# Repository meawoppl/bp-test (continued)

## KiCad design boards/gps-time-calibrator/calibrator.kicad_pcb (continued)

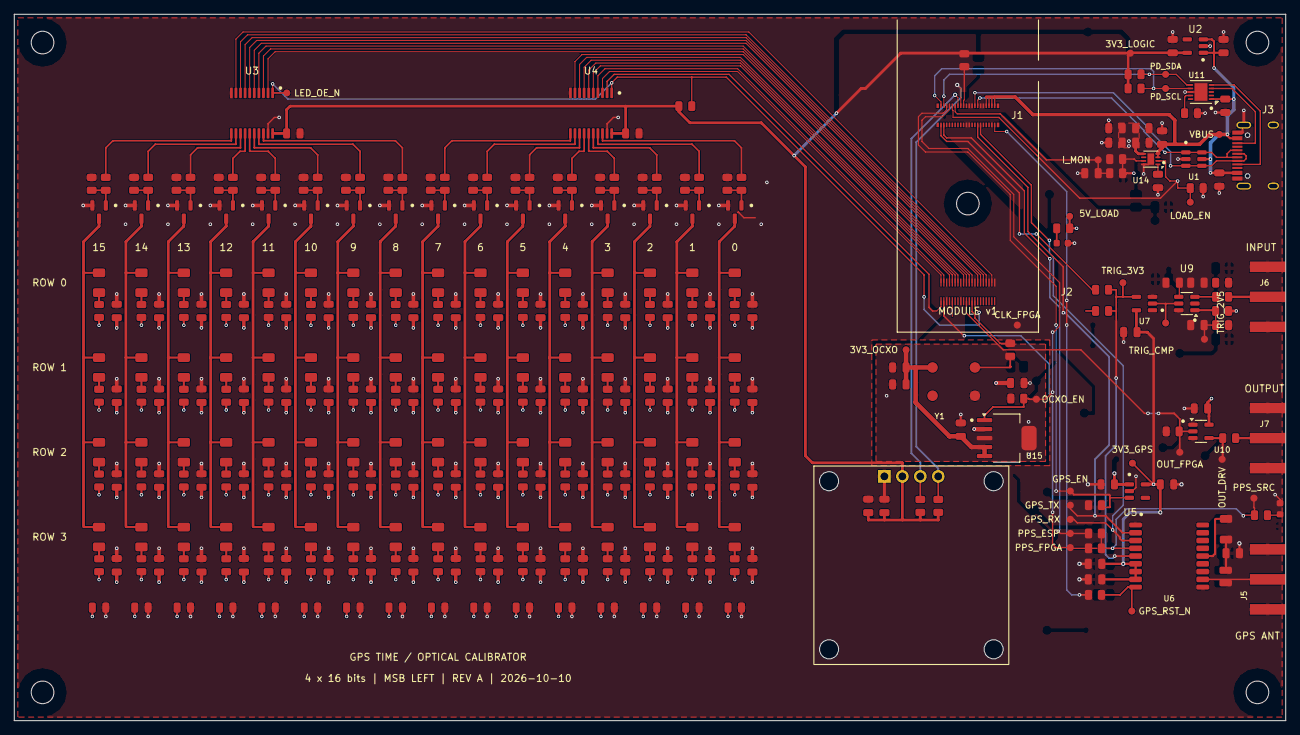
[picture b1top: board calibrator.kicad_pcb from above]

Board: 4 copper layers, 180.0 x 100.0 mm, 365 parts (0 on the bottom side), 175 nets.

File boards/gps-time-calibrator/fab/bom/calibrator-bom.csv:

Comment,Designator,Quantity,Footprint,MPN,LCSC Part #,Supplier URL
100nF,"C1,C4,C5,C8,C11,C13,C14,C15,C20,C21,C22,C23,C24,C25,C26,C27,C28,C29,C30,C31,C32,C33,C34,C35,C68,C69,C73,C76,C78",29,Calibrator:C_0805_2012Metric,CL21B104KBCNNNC,C1711,https://www.lcsc.com/product-detail/C1711.html
4.7uF,"C2,C3,C6,C7,C9,C65,C66",7,Calibrator:C_0805_2012Metric,CL21A475KAQNNNE,C1779,https://www.lcsc.com/product-detail/C1779.html
10nF,C10,1,Calibrator:C_0805_2012Metric,CL21B103KBANNNC,C1710,https://www.lcsc.com/product-detail/C1710.html
10uF / 10uF / 25V,"C40,C41,C42,C43,C44,C45,C46,C47,C48,C49,C50,C51,C52,C53,C54,C55,C60,C61,C62,C63,C70,C74,C77",23,Calibrator:C_0805_2012Metric,CL21A106KAYNNNE,C15850,https://www.lcsc.com/product-detail/C15850.html
1uF,C64,1,Calibrator:C_0805_2012Metric,CL21B105KBFNNNE,C28323,https://www.lcsc.com/product-detail/C28323.html
22uF / 25V,C71,1,Calibrator:C_0805_2012Metric,CL21A226MAQNNNE,C45783,https://www.lcsc.com/product-detail/C45783.html
1nF,C75,1,Calibrator:C_0805_2012Metric,0805CG102J500NT,C29925,https://www.lcsc.com/product-detail/C29925.html
GREEN,"D1,D74",2,Calibrator:LED_0603_1608Metric,XL-1608SYGC-06,C965805,https://www.lcsc.com/product-detail/C965805.html
GREEN,"D10,D11,D12,D13,D14,D15,D16,D17,D18,D19,D20,D21,D22,D23,D24,D25,D26,D27,D28,D29,D30,D31,D32,D33,D34,D35,D36,D37,D38,D39,D40,D41,D42,D43,D44,D45,D46,D47,D48,D49,D50,D51,D52,D53,D54,D55,D56,D57,D58,D59,D60,D61,D62,D63,D64,D65,D66,D67,D68,D69,D70,D71,D72,D73",64,Calibrator:LED_1206_3216Metric,YLED1206G,C30584801,https://www.lcsc.com/product-detail/C30584801.html
DF40C-40DP-0.4V(51),J1,1,Calibrator:J1_Module_v1_Mate,DF40C-40DP-0.4V(51),C424643,https://www.lcsc.com/product-detail/C424643.html
DF40C(2.0)-40DS-0.4V(51),J2,1,Calibrator:J2_Module_v1_Mate,DF40C(2.0)-40DS-0.4V(51),C597934,https://www.lcsc.com/product-detail/C597934.html
USB-C 5V/3A + DATA,J3,1,Calibrator:USB_C_Receptacle_HRO_TYPE-C-31-M-12,TYPE-C-31-M-12,C165948,https://www.lcsc.com/product-detail/C165948.html
GPS ANTENNA / INPUT 5V / 2.5V THRESHOLD / FPGA OUTPUT 5V,"J5,J6,J7",3,Calibrator:SMA_Amphenol_132289_EdgeMount,132289,C3172723,https://www.lcsc.com/product-detail/C3172723.html
61300411121,J8,1,Calibrator:OLED_Header_1x04_P2.54mm,61300411121,C5184785,https://www.lcsc.com/product-detail/C5184785.html
27nH,L1,1,Calibrator:L_Coilcraft_0805CS,0805CS-270XGLC,C38841159,https://www.lcsc.com/product-detail/C38841159.html
AO3400A,"Q1,Q2,Q3,Q4,Q5,Q6,Q7,Q8,Q9,Q10,Q11,Q12,Q13,Q14,Q15,Q16",16,Calibrator:SOT-23,AO3400A,C20917,https://www.lcsc.com/product-detail/C20917.html
2.2k,R3,1,Calibrator:R_0805_2012Metric,0805W8F2201T5E,C17520,https://www.lcsc.com/product-detail/C17520.html
100k,"R4,R9,R120,R121,R122,R123,R124,R125,R126,R127,R128,R129,R130,R131,R132,R133,R134,R135,R163,R169,R176,R177,R178",23,Calibrator:R_0805_2012Metric,RC0805FR-07100KL,C96346,https://www.lcsc.com/product-detail/C96346.html
10R 0.25W,R5,1,Calibrator:R_1206_3216Metric,1206W4F100JT5E,C17903,https://www.lcsc.com/product-detail/C17903.html
33R,"R6,R7,R162,R173,R180",5,Calibrator:R_0805_2012Metric,0805W8F330JT5E,C17634,https://www.lcsc.com/product-detail/C17634.html
1k,"R8,R179",2,Calibrator:R_0805_2012Metric,0805W8F1001T5E,C17513,https://www.lcsc.com/product-detail/C17513.html
470R 1%,"R10,R11,R12,R13,R14,R15,R16,R17,R18,R19,R20,R21,R22,R23,R24,R25,R26,R27,R28,R29,R30,R31,R32,R33,R34,R35,R36,R37,R38,R39,R40,R41,R42,R43,R44,R45,R46,R47,R48,R49,R50,R51,R52,R53,R54,R55,R56,R57,R58,R59,R60,R61,R62,R63,R64,R65,R66,R67,R68,R69,R70,R71,R72,R73",64,Calibrator:R_0805_2012Metric,0805W8F4700T5E,C17710,https://www.lcsc.com/product-detail/C17710.html
100R,"R80,R81,R100,R101,R102,R103,R104,R105,R106,R107,R108,R109,R110,R111,R112,R113,R114,R115",18,Calibrator:R_0805_2012Metric,RC0805FR-07100RL,C105577,https://www.lcsc.com/product-detail/C105577.html
10k,"R140,R160,R161,R167,R168",5,Calibrator:R_0805_2012Metric,0805W8F1002T5E,C17414,https://www.lcsc.com/product-detail/C17414.html
22.6k,R164,1,Calibrator:R_0805_2012Metric,SCR0805F22K6,C3016901,https://www.lcsc.com/product-detail/C3016901.html
820R,R170,1,Calibrator:R_0805_2012Metric,0805W8F8200T5E,C17837,https://www.lcsc.com/product-detail/C17837.html
4.7k,"R174,R175",2,Calibrator:R_0805_2012Metric,0805W8F4701T5E,C17673,https://www.lcsc.com/product-detail/C17673.html
USBLC6-2SC6,U1,1,Calibrator:SOT-23-6_U1,USBLC6-2SC6,C7519,https://www.lcsc.com/product-detail/C7519.html
AP2112K-3.3,"U2,U5,U12",3,Calibrator:SOT-23-5,AP2112K-3.3TRG1,C51118,https://www.lcsc.com/product-detail/C51118.html
SN74LVC541APWR,"U3,U4",2,Calibrator:TSSOP-20_4.4x6.5mm_P0.65mm,SN74LVC541APWR,C113281,https://www.lcsc.com/product-detail/C113281.html
MAX-M10S-00B-01,U6,1,Calibrator:ublox_MAX,MAX-M10S-00B-01,C24834155,https://www.lcsc.com/product-detail/C24834155.html
SN74LVC1G17DBVR,U7,1,Calibrator:SOT-23-5,SN74LVC1G17DBVR,C7836,https://www.lcsc.com/product-detail/C7836.html
TLV3501AIDBVR,U9,1,Calibrator:SOT-23-6_U9,TLV3501AIDBVR,C193413,https://www.lcsc.com/product-detail/C193413.html
SN74AHCT1G125DBVR,U10,1,Calibrator:SOT-23-5_U10,SN74AHCT1G125DBVR,C7484,https://www.lcsc.com/product-detail/C7484.html
HUSB238_002DD,U11,1,Calibrator:HUSB238_DFN10_3x3mm,HUSB238_002DD,C7471904,https://www.lcsc.com/product-detail/C7471904.html
TPS259531DSGR,U14,1,Calibrator:DFN-8-1EP_2x2mm_P0.5mm_EP0.9x1.6mm,TPS259531DSGR,C2155674,https://www.lcsc.com/product-detail/C2155674.html
TPS7A4533DCQR,U15,1,Calibrator:SOT-223-6,TPS7A4533DCQR,C2877942,https://www.lcsc.com/product-detail/C2877942.html
HS96L03W2C03,DS1,1,Calibrator:HS96L03W2C03_27.3x27.8mm,HS96L03W2C03,,https://www.lcsc.com/product-detail/C5248080.html
AOC97FAJC-10.0000,Y1,1,Calibrator:AOC97_9.7x7.5mm,AOC97FAJC-10.0000,,https://www.digikey.com/en/products/detail/abracon-llc/AOC97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

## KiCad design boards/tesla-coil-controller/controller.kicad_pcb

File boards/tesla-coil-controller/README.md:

# Tesla coil controller — acquisition-first development board

**A0 development draft, not a complete controller or fabrication release.** Registered as
`tesla-coil-controller` in the workspace selector. The current board contains the module
interface, acquisition circuit, CST conditioning, and first-pass step-down circuits. Two 24 V GDT full bridges are included, with routed power and gate-drive circuits; the remaining regulator/ESP32/analog routing, input protection and bench qualification remain. J6 has been removed.

Uses the ordered [ESP32-S2/iCE40UP5K module v1 ICD](https://github.com/OrbitalCommons/gumstick/blob/main/current-df40-connectors/docs/ICD-v1.md)
and the programmer's exact, renumbered mating footprints. J1/J2 centers are 25 mm apart;
H1 is their midpoint. Correct module outline is shown on Dwgs.User, with 2 mm mating height.

The current 163 × 141.8 mm, two-layer board puts CST and battery connectors on the left edge, acquisition and the module at the top edge, and both GDT outputs on the right edge. Battery entry and both auxiliary power modules occupy the upper-left. The compact AUX stages sit below them, with two wide CST stages underneath; the ADC sits just below the FPGA connector, with GDT stages in a separate column to the right. Silkscreen regions group each circuit and its support components; see [the floorplan](docs/FLOORPLAN.md).
The consolidated power/CST placement and local 2.5 mm GDT output links are described in the floorplan notes; substantial routing remains.
0603 resistors/capacitors around the ADC; larger passives elsewhere, exposed-lead LQFP ADC. No final stackup or impedance claim.

## Acquisition selected

AD7606C-16BSTZ, eight simultaneous 16-bit channels, LQFP-64 10 × 10 mm, 0.5 mm pitch.
LCSC C5371769. Channels 5/6 measure CST 1 raw current / rectified amplitude; channels 7/8 do the same for CST 2. Channels 1–4 are external 0–5 V inputs on J3/J8/J9/J10. All channels sample on the same CONVST edge. Four serial output
lanes go directly to the FPGA, independent of the internal ESP32–FPGA communications bus.

See [ADC research and timing](docs/ADC-SELECTION.md), [architecture and open decisions](docs/ARCHITECTURE.md),
[exact daughterboard contact assignment](docs/daughterboard-pinout.csv), and
[component/net contract](docs/circuit.json).

**J4 and J30 each accept one 12 V battery; the PCB joins them in series for 24 V nominal.** J4 is the upper battery and J30 the lower battery; pin 1 is positive on both. J4.2 connects only to J30.1 through `BAT_MID_12V`. Alternatively, connect one 24 V PSU between J4.1 (+) and J30.2 (−), leaving the two midpoint terminals unused. See the [series-input review and checks](docs/series-battery-input-review.txt). The GDT bridges use the battery rail directly. U30/U31 LMZ14202H modules independently generate 12 V bias and module/ADC 5 V directly from the battery rail. The main 24 V converter and its 27 components were removed. The +5 V/+12 V distribution and AUX −5 V extension are routed; battery input and 3.3 V distribution are now also connected. No rails are bench-validated.
See [power calculations](docs/POWER-DESIGN.md) and the accepted [24 V decision](docs/DRIVE-DECISION.md).
J3/J8/J9/J10 expect already conditioned voltage signals, **not a bare current transformer**.
Its 100R/1nF networks are EMI placeholders, not a complete anti-alias filter or surge protector.

## Files and status

- `controller.kicad_pro/.kicad_sch/.kicad_pcb`: native project, acquisition/power schematic and partially routed layout.
- `Tesla.kicad_sym`, `Tesla.pretty`, local model files: initial project-local libraries.
- `docs/datasheets`: selected ADC datasheet and supplied reference schematic.
- `fab/checks`: latest draft checks. Airwires are expected; no Gerbers/BOM/CPL are offered for ordering.
- `tools/hardware/build_tesla_controller.py`: initial constructor, refuses overwrite without `--replace-draft`.
- `tools/hardware/tesla_schematic.py`: schematic generation and exact native-netlist pad-net synchronization.

Do not rerun the placement constructor over later routing. Unused daughterboard contacts are
explicitly NC; changing a carrier assignment never changes the frozen module pinout.

## Circuit views

- [Subsystem diagram](docs/subsystems.svg): solid blocks exist in the schematic;
  dashed blocks are planned circuitry or external equipment. This is not a completed driver.
- [Readable schematic PDF](docs/controller-schematic.pdf): connected switching,
  feedback, filter and bypass circuits with grouped support components.
- [Presentation validation](docs/schematic-presentation-validation.json): unchanged
  electrical netlist, pin names/numbers and PCB; zero ERC violations.

Rebuild the presentation with `/usr/bin/python3 tools/hardware/tesla_schematic.py`.
It validates the result against `docs/circuit.json` and does not write the PCB.
Rebuild the diagram with `python3 tools/hardware/tesla_subsystems.py`.

## CST front end

[Design and simulation notes](docs/CST-INPUT.md) cover the 10-ohm burden, ±2 V nominal raw signal, precision full-wave magnitude channel, independent phase comparator. [Simulation plot](docs/cst/rectifier-topology.png). Overcurrent decisions belong to the ADC/FPGA. See [output-stage design](docs/OUTPUT-STAGE.md) and [simulation](docs/gdt/transient-sweep.png). The board is partially routed.

J3/J8/J9/J10 now join the CST connectors on the left edge. Their four AUX channels have unity-gain buffers, input clamps and filtering; see [AUX inputs](docs/AUX-INPUTS.md).

CST routing milestone: two copper layers, both sensor front ends and the shared −5 V converter locally connected; The four analog ADC handoffs remain deliberately open; both phase-comparator returns now reach the FPGA. See [CST routing and validation](docs/CST-ROUTING.md).

Positive supply routing: all +5 V and +12 V distribution pads are connected, including the ADC and filtered AUX branches. See [power routing, checks and remaining work](docs/POWER-ROUTING.md).

AUX routing: all four connectors, filters, unity buffers and ADC CH1–4 links are connected, including negative-supply extensions and bypass returns. See [AUX routing](docs/AUX-ROUTING.md).

FPGA routing: all assigned FPGA data/control contacts and downstream driver connections are routed on two layers. Five ADC carrier pin assignments changed for fanout order; firmware constraints must use the updated [contact map](docs/daughterboard-pinout.csv). See [FPGA routing and current checks](docs/FPGA-ROUTING.md). Whole-board routing is still incomplete; see the current counts in [validation.json](docs/validation.json).

H-bridge routing: both stages, drivers, bootstrap/gate networks, reservoirs and battery feeds are connected. The low-side gate-output net names were corrected to keep 12 V outputs separate from raw FPGA commands. See [H-bridge routing and validation](docs/HBRIDGE-ROUTING.md).

Latest cleanup: [command routing, ADC fanout and supply placement](docs/COMMAND-AND-ADC-CLEANUP.md). U50/U55 and the shared enable path are removed; FPGA fabric owns blanking and drive timing. The ARM indicator and J6 service header are removed. Replay current copper with `tools/hardware/tesla_route_reviewed.py`; historical incremental routing scripts describe older circuits.

ADC reference and regulator capacitors C6–C9 are connected, closing five opens; six unrelated connections remain. See [routing review](docs/adc-passives-review.txt), [copper preview](docs/adc-passives-after.png) and [verification](docs/adc-passives-verification.json).

CT2_HALF at TP61 now stays on front copper, eliminating two vias and shortening the route by 6.29 mm. See [trace review](docs/ct2-half-front-review.txt), [copper preview](docs/ct2-half-front-after.png) and [verification](docs/ct2-half-front-verification.json).

Local indicators: [rail-presence and directly sensed H-bridge legs](docs/INDICATORS.md). The buffered LED bank and dedicated FPGA LED/status assignments are removed. The lamps are distributed beside their supplies and half-bridge drivers.

D42 now sits above D41 to match the other CST stack, with clearance to C420. Its two front-copper nets use four fewer vias. See [placement review](docs/d42-placement-review.txt), [preview](docs/d42-placement-after.png) and [verification](docs/d42-placement-verification.json).

J5 is the library HRO TYPE-C-31-M-12 USB-C receptacle, **for programming only**. It connects to the module’s native ESP32-S2 USB data pins; power the controller from its normal supply. Host VBUS is isolated from VIN_5V and feeds only ESD protection and a sense divider on J1.20 (ESP GPIO8). Firmware must configure that GPIO as the self-powered USB VBUS monitor; this edit does not change firmware. See [USB-C review and checks](docs/usb-c-review.txt) and [connector contacts](docs/usb-header-pinout.csv).

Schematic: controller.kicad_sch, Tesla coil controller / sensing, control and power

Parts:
C1, C2, C3, C4, C5, C8: 100nF; C_0603_1608Metric
C6, C7, C20, C21: 1uF; C_0603_1608Metric
C9, C10: 10uF; C_0603_1608Metric
C11, C12, C13, C14, C15, C16, C17, C18: 1nF; C_0603_1608Metric
C22: 100nF / 16V; C_0603_1608Metric; MPN CL10B104KO8NNNC; LCSC C14663
C300, C310: 4.7nF; C_0805_2012Metric
C301, C311: 22nF; C_0805_2012Metric
C302, C303, C312, C313: 10uF 50V X7R; C_1210_3225Metric
C304, C305, C306, C314, C315, C316: 47uF 25V X7R; C_1210_3225Metric
C335, C336, C337, C338, C339, C340, C341, C342, C526, C531, C532, C533, C534, C535, C536, C537, C566, C571, C572, C573, C574, C575, C576, C577: 22uF 50V X7R; C_2220_5750Metric; MPN CGA9P3X7R1H226MT0Y0N; LCSC C49297044
C400, C600: 10nF C0G; C_0805_2012Metric
C401, C402, C403, C404, C413, C601, C602, C603, C604, C613: 100nF; C_0805_2012Metric
C410, C610: 22pF C0G; C_0805_2012Metric
C412, C612: 1uF; C_0805_2012Metric
C420, C421, C425, C625: 1uF 16V; C_0805_2012Metric
C422, C423: 10uF 16V; C_0805_2012Metric
C424, C624: 2.2uF; C_0805_2012Metric
C427, C428, C627, C628, C700, C710, C720, C730: 150pF 50V C0G; C_0805_2012Metric
C429, C629: 1nF 50V C0G; C_0805_2012Metric
C520, C523, C560, C563: 1uF 25V X7R; C_0805_2012Metric
C521, C524, C561, C564: 100nF 25V; C_0805_2012Metric
C522, C525, C562, C565: 4.7uF 25V X7R; C_0805_2012Metric
C529, C569: 2.2uF 50V X7R; C_1210_3225Metric; MPN C3225X7R1H225KT000N; LCSC C76683
C530, C570: 1uF 50V X7R; C_1206_3216Metric; MPN C1206C105K5RACTU; LCSC C2167287
C701, C711, C721, C731: 2.2nF 50V C0G; C_0805_2012Metric
C702, C712, C722, C732: 100nF 25V X7R; C_0805_2012Metric
C703, C713, C723, C733: 100nF 16V X7R; C_0805_2012Metric
C740: 10uF 25V X7R; C_0805_2012Metric
C741: 10uF 16V X7R; C_0805_2012Metric
D40, D60: SMBJ5.0CA; D_SMB; MPN SMBJ5.0CA
D41, D42, D61, D62, D90, D91, D92, D93: 1N4148W,115; D_SOD-123; MPN 1N4148W,115
D43, D63: BAT54S,215; SOT-23; MPN BAT54S,215
D50, D51: SMBJ30A; D_SMB; MPN SMBJ30A-13-F
D70, D71, D72, D73: BAV199,215; SOT-23; MPN BAV199,215
D80, D81, D82, D83, D84, D86, D87, D88: GREEN; LED_0805_2012Metric; MPN KT-0805G; LCSC C2297
H1: M3 module mounting; MountingHole_3.2mm_M3
H2, H3, H4, H5: M3; MountingHole_3.2mm_M3
J1: DF40C-40DP-0.4V(51); J1_Module_v1_Mate; MPN DF40C-40DP-0.4V(51); LCSC C424643
J2: DF40C(2.0)-40DS-0.4V(51); J2_Module_v1_Mate; MPN DF40C(2.0)-40DS-0.4V(51); LCSC C597934
J3: AUX 1 / 0-5V; JST_PH_S2B-PH-K_1x02_P2.00mm_Horizontal; MPN S2B-PH-K-S(LF)(SN)
J4: 12V BATTERY / UPPER; TerminalBlock_Phoenix_MKDS-1,5-2-5.08_1x02_P5.08mm_Horizont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
J5: USB-C / PROGRAMMING ONLY; USB_C_Receptacle_HRO_TYPE-C-31-M-12; MPN TYPE-C-31-M-12; LCSC C165948
J8: AUX 2 / 0-5V; JST_PH_S2B-PH-K_1x02_P2.00mm_Horizontal; MPN S2B-PH-K-S(LF)(SN)
J9: AUX 3 / 0-5V; JST_PH_S2B-PH-K_1x02_P2.00mm_Horizontal; MPN S2B-PH-K-S(LF)(SN)
J10: AUX 4 / 0-5V; JST_PH_S2B-PH-K_1x02_P2.00mm_Horizontal; MPN S2B-PH-K-S(LF)(SN)
J30: 12V BATTERY / LOWER; TerminalBlock_Phoenix_MKDS-1,5-2-5.08_1x02_P5.08mm_Horizont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
J40: CST SECONDARY; TerminalBlock_Phoenix_MKDS-1,5-2-5.08_1x02_P5.08mm_Horizont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
J50: GDT 1 PRIMARY; TerminalBlock_Phoenix_MKDS-1,5-2-5.08_1x02_P5.08mm_Horizont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
J51: GDT 2 PRIMARY; TerminalBlock_Phoenix_MKDS-1,5-2-5.08_1x02_P5.08mm_Horizont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
J60: CST 2 SECONDARY; TerminalBlock_Phoenix_MKDS-1,5-2-5.08_1x02_P5.08mm_Horizont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
L40, L60: 90R @100MHz / 2A CMC; CMC_TAI-TECH_WCM4532F2SF; MPN WCM4532F2SF-900T20; LCSC C357325
Q50, Q51, Q52, Q53, Q54, Q55, Q56, Q57: STD80N10F7; TO-252-2; MPN STD80N10F7; LCSC C2832811
R1, R2, R3, R4, R5, R6, R7, R8: 100R; R_0603_1608Metric
R20: 0R; R_0603_1608Metric
R21, R22, R23: 10k; R_0603_1608Metric
R24, R25: 5.1k; R_0603_1608Metric; MPN 0603WAF5101T5E; LCSC C23186
R26: 100k; R_0603_1608Metric; MPN 0603WAF1003T5E; LCSC C25803
R27: 150k; R_0603_1608Metric; MPN 0603WAF1503T5E; LCSC C22807
R300, R310: 34k; R_0805_2012Metric
R301: 2.43k; R_0805_2012Metric
R302: 249k; R_0805_2012Metric
R304, R314: 168k; R_0805_2012Metric
R305, R315, R521, R523, R525, R527, R561, R563, R565, R567: 10k; R_0805_2012Metric
R311: 6.49k; R_0805_2012Metric
R312: 100k; R_0805_2012Metric
R400, R401, R600, R601: 20R 1% 1W; R_2512_6332Metric; MPN CRCW251220R0FKEG
R402, R403, R404, R405, R406, R407, R411, R422, R602, R603, R604, R605, R606, R607, R611, R622: 10k 0.1%; R_0805_2012Metric
R408, R608: 1k; R_0805_2012Metric
R410, R610: 5k 0.1%; R_0805_2012Metric
R414, R415, R614, R615, R700, R710, R720, R730: 1k 0.1%; R_0805_2012Metric
R416, R505, R506, R507, R508, R513, R514, R515, R516, R616: 33R; R_0805_2012Metric
R421, R740: 10R; R_0805_2012Metric
R500, R501, R502, R503, R509, R510, R511, R512: 2.2k; R_0805_2012Metric
R520, R522, R524, R526, R560, R562, R564, R566: 4.7R; R_0805_2012Metric
R529, R569: 15R 1W; R_2512_6332Metric
R701, R711, R721, R731: 1M 1%; R_0805_2012Metric
R800, R804, R806, R807, R808: 12k; R_0805_2012Metric
R801: 5.1k; R_0805_2012Metric
R802: 1.5k; R_0805_2012Metric
R803: 680R; R_0805_2012Metric
TP1: ADC_FIRST; TestPoint_Pad_D1.0mm
TP40: CT1_RAW; TestPoint_Pad_D1.0mm
TP41: CT1_HALF; TestPoint_Pad_D1.0mm
TP42: CT1_ABS; TestPoint_Pad_D1.0mm
TP43: CT1_ENVELOPE; TestPoint_Pad_D1.0mm
TP60: CT2_RAW; TestPoint_Pad_D1.0mm
TP61: CT2_HALF; TestPoint_Pad_D1.0mm
TP62: CT2_ABS; TestPoint_Pad_D1.0mm
TP63: CT2_ENVELOPE; TestPoint_Pad_D1.0mm
TP700: AUX1_0_5V; TestPoint_Pad_D1.0mm_Silk0.15mm
TP701: AUX1_BUFFERED; TestPoint_Pad_D1.0mm_Silk0.15mm
TP702, TP712, TP722, TP732: GND; TestPoint_Pad_D1.0mm_Silk0.15mm
TP710: AUX2_0_5V; TestPoint_Pad_D1.0mm_Silk0.15mm
TP711: AUX2_BUFFERED; TestPoint_Pad_D1.0mm_Silk0.15mm
TP720: AUX3_0_5V; TestPoint_Pad_D1.0mm_Silk0.15mm
TP721: AUX3_BUFFERED; TestPoint_Pad_D1.0mm_Silk0.15mm
TP730: AUX4_0_5V; TestPoint_Pad_D1.0mm_Silk0.15mm
TP731: AUX4_BUFFERED; TestPoint_Pad_D1.0mm_Silk0.15mm
U1: AD7606C-16BSTZ; LQFP-64_10x10mm_P0.5mm; MPN AD7606C-16BSTZ; LCSC C5371769
U2: AP2112K-3.3; SOT-23-5; MPN AP2112K-3.3TRG1; LCSC C51118
U3: USBLC6-2SC6; SOT-23-6; MPN USBLC6-2SC6; LCSC C7519
U30, U31: LMZ14202HTZX/NOPB; Texas_NDW-7_TabPin8; MPN LMZ14202HTZX/NOPB; LCSC C2861493
U40, U41, U60, U61, U70, U71, U72, U73: OPA197IDBVR; SOT-23-5; MPN OPA197IDBVR
U42, U62: TLV3501AIDBVR; SOT-23-6; MPN TLV3501AIDBVR
U44: TPS60403DBVR; SOT-23-5; MPN TPS60403DBVR
U51, U52, U53, U54: UCC27282DR; SOIC-8_3.9x4.9mm_P1.27mm; MPN UCC27282DR; LCSC C2867844

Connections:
+3V3: C5.1, C21.1, C413.1, C424.1, C613.1, C624.1, D43.2 (K2), D63.2 (K2), R22.1, R23.1, R411.1, R414.1, R611.1, R614.1, R803.1, U1.3 (OS0), U1.4 (OS1), U1.5 (OS2), U1.6 (PAR_SER), U1.7 (STBY_N), U1.10 (WR_N), U1.23 (+3V3), U1.34 (REFSEL), U2.5 (VOUT), U42.4 (V+), U62.4 (V+)
+5V_ADC: C1.1, C2.1, C3.1, C4.1, C10.1, C401.1, C403.1, C421.1, C601.1, C603.1, D70.2 (K2), D71.2 (K2), D72.2 (K2), D73.2 (K2), R20.2, U1.1 (AVCC), U1.37 (AVCC), U1.38 (AVCC), U1.48 (AVCC), U40.5 (V+), U41.5 (V+), U44.2 (IN), U60.5 (V+), U61.5 (V+)
+12V_AUX: C702.1, C712.1, C722.1, C732.1, C740.1, R740.2, U70.5 (V+), U71.5 (V+), U72.5 (V+), U73.5 (V+)
+12V_BIAS: C301.1, C304.1, C305.1, C306.1, C521.1, C522.1, C524.1, C525.1, C561.1, C562.1, C564.1, C565.1, R300.1, R740.1, R801.1, U30.7 (VOUT), U51.1 (VDD), U52.1 (VDD), U53.1 (VDD), U54.1 (VDD)
-5V_CT: C402.1, C404.1, C423.1, C602.1, C604.1, C703.1, C713.1, C723.1, C733.1, C741.1, R421.2, U40.2 (V-), U41.2 (V-), U60.2 (V-), U61.2 (V-), U70.2 (V-), U71.2 (V-), U72.2 (V-), U73.2 (V-)
ADC_BUSY: J2.35 (FPGA_IOB_0A), U1.14 (ADC_BUSY)
ADC_CH1: C11.1, R1.2, U1.49 (V1+)
ADC_CH2: C12.1, R2.2, U1.51 (V2+)
ADC_CH3: C13.1, R3.2, U1.53 (V3+)
ADC_CH4: C14.1, R4.2, U1.55 (V4+)
ADC_CH5: C15.1, R5.2, U1.57 (V5+)
ADC_CH6: C16.1, R6.2, U1.59 (V6+)
ADC_CH7: C17.1, R7.2, U1.61 (V7+)
ADC_CH8: C18.1, R8.2, U1.63 (V8+)
ADC_CONVST: J2.31 (FPGA_IOT_49A), R21.2, U1.9 (ADC_CONVST)
ADC_CS_N: J2.34 (FPGA_IOB_5B), R22.2, U1.13 (ADC_CS_N)
ADC_DOUT_A: J2.40 (FPGA_IOB_6A), U1.24 (ADC_DOUT_A)
ADC_DOUT_B: J2.39 (FPGA_IOB_8A), U1.25 (ADC_DOUT_B)
ADC_DOUT_C: J2.38 (FPGA_IOB_9B), U1.27 (ADC_DOUT_C)
ADC_DOUT_D: J2.37 (FPGA_IOB_4A), U1.28 (ADC_DOUT_D)
ADC_FIRST: TP1.1, U1.15 (ADC_FIRST)
ADC_REFCAP: C9.1, U1.44 (ADC_REFCAP), U1.45 (ADC_REFCAP)
ADC_REF_2V5: C8.1, U1.42 (ADC_REF_2V5)
ADC_RESET: J2.32 (FPGA_IOB_3B_G6), R23.2, U1.11 (ADC_RESET)
ADC_SCLK: J2.33 (FPGA_IOT_44B), U1.12 (ADC_SCLK)
ADC_SDI: J2.36 (FPGA_IOB_2A), U1.29 (ADC_SDI)
AUX1_0_5V: C700.1, J3.1 (AUX1), R700.1, R701.1, TP700.1
AUX1_BUFFERED: R1.1, TP701.1, U70.1 (OUT), U70.4 (-)
AUX1_FILTERED: C701.1, D70.3 (K1/A2), R700.2, U70.3 (+)
AUX2_0_5V: C710.1, J8.1 (AUX2), R710.1, R711.1, TP710.1
AUX2_BUFFERED: R2.1, TP711.1, U71.1 (OUT), U71.4 (-)
AUX2_FILTERED: C711.1, D71.3 (K1/A2), R710.2, U71.3 (+)
AUX3_0_5V: C720.1, J9.1 (AUX3), R720.1, R721.1, TP720.1
AUX3_BUFFERED: R3.1, TP721.1, U72.1 (OUT), U72.4 (-)
AUX3_FILTERED: C721.1, D72.3 (K1/A2), R720.2, U72.3 (+)
AUX4_0_5V: C730.1, J10.1 (AUX4), R730.1, R731.1, TP730.1
AUX4_BUFFERED: R4.1, TP731.1, U73.1 (OUT), U73.4 (-)
AUX4_FILTERED: C731.1, D73.3 (K1/A2), R730.2, U73.3 (+)
BAT_MID_12V: J4.2 (-), J30.1 (+)
CT1_ABS: R407.2, R408.1, TP42.1, U41.1 (OUT)
CT1_ABS_SUM: R404.2, R405.2, R406.2, R407.1, U41.4 (-)
CT1_CABLE_N: C428.1, J40.2 (S2 / RETURN), L40.4 (N IN)
CT1_CABLE_P: C427.1, J40.1 (S1 / DOT), L40.1 (P IN)
CT1_ENVELOPE: C400.1, R6.1, R408.2, TP43.1
CT1_FLY_N: C420.2, U44.3 (CFLY-)
CT1_FLY_P: C420.1, U44.5 (CFLY+)
CT1_HALF: D42.2 (A), R403.2, R405.1, R406.1, TP41.1
CT1_MID: C412.1, R414.2, R415.1, U42.1 (-)
CT1_NEG_PUMP: C422.1, R421.1, U44.1 (OUT)
CT1_PHASE: C410.1, D43.3 (K1/A2), R410.2, R411.2, R422.1, U42.3 (+)
CT1_PHASE_AC: C425.2, R410.1
CT1_RAW: C425.1, C429.1, D40.1, L40.2 (P OUT), R5.1, R400.1, R401.1, R402.1, R404.1, TP40.1
CT1_RECT_DRIVE: D41.2 (A), D42.1 (K), U40.1 (OUT)
CT1_RECT_SUM: D41.1 (K), R402.2, R403.1, U40.4 (-)
CT1_ZERO: J2.22 (FPGA_IOT_46B_G0), R416.2
CT1_ZERO_DRV: R416.1, U42.5 (OUT)
CT2_ABS: R607.2, R608.1, TP62.1, U61.1 (OUT)
CT2_ABS_SUM: R604.2, R605.2, R606.2, R607.1, U61.4 (-)
CT2_CABLE_N: C628.1, J60.2 (S2 / RETURN), L60.4 (N IN)
CT2_CABLE_P: C627.1, J60.1 (S1 / DOT), L60.1 (P IN)
CT2_ENVELOPE: C600.1, R8.1, R608.2, TP63.1
CT2_HALF: D62.2 (A), R603.2, R605.1, R606.1, TP61.1
CT2_MID: C612.1, R614.2, R615.1, U62.1 (-)
CT2_PHASE: C610.1, D63.3 (K1/A2), R610.2, R611.2, R622.1, U62.3 (+)
CT2_PHASE_AC: C625.2, R610.1
CT2_RAW: C625.1, C629.1, D60.1, L60.2 (P OUT), R7.1, R600.1, R601.1, R602.1, R604.1, TP60.1
CT2_RECT_DRIVE: D61.2 (A), D62.1 (K), U60.1 (OUT)
CT2_RECT_SUM: D61.1 (K), R602.2, R603.1, U60.4 (-)
CT2_ZERO: J2.24 (FPGA_IOT_45A_G1), R616.2
CT2_ZERO_DRV: R616.1, U62.5 (OUT)
GDT1_L_HB: C520.1, U51.2 (HB)
GDT1_L_HG: Q50.1 (G), R520.2, R521.1
GDT1_L_HI: J2.7 (FPGA_IOB_20A), R500.1, R505.1
GDT1_L_HI_BUS: R505.2, U51.5 (HI)
GDT1_L_HO: R520.1, U51.3 (HO)
GDT1_L_LG: Q51.1 (G), R522.2, R523.1
GDT1_L_LO: J2.9 (FPGA_IOT_37A), R501.1, R506.1
GDT1_L_LO_BUS: R506.2, U51.6 (LI)
GDT1_L_LO_DRV: R522.1, U51.8 (LO)
GDT1_L_SW: C520.2, C529.1, Q50.3 (S), Q51.2 (D), R521.2, R529.1, R804.1, U51.4 (HS)
GDT1_OUT_P: C529.2, C530.2, J50.1 (PRIMARY +)
GDT1_R_HB: C523.1, U52.2 (HB)
GDT1_R_HG: Q52.1 (G), R524.2, R525.1
GDT1_R_HI: J2.10 (FPGA_IOB_23B), R502.1, R507.1
GDT1_R_HI_BUS: R507.2, U52.5 (HI)
GDT1_R_HO: R524.1, U52.3 (HO)
GDT1_R_LG: Q53.1 (G), R526.2, R527.1
GDT1_R_LO: J2.11 (FPGA_IOB_29B), R503.1, R508.1
GDT1_R_LO_BUS: R508.2, U52.6 (LI)
GDT1_R_LO_DRV: R526.1, U52.8 (LO)
GDT1_R_SW: C523.2, J50.2 (PRIMARY -), Q52.3 (S), Q53.2 (D), R525.2, R806.1, U52.4 (HS)
GDT1_SNUB: C530.1, R529.2
GDT2_L_HB: C560.1, U53.2 (HB)
GDT2_L_HG: Q54.1 (G), R560.2, R561.1
GDT2_L_HI: J2.2 (FPGA_IOB_18A), R509.1, R513.1
GDT2_L_HI_BUS: R513.2, U53.5 (HI)
GDT2_L_HO: R560.1, U53.3 (HO)
GDT2_L_LG: Q55.1 (G), R562.2, R563.1
GDT2_L_LO: J2.4 (FPGA_IOB_16A), R510.1, R514.1
GDT2_L_LO_BUS: R514.2, U53.6 (LI)
GDT2_L_LO_DRV: R562.1, U53.8 (LO)
GDT2_L_SW: C560.2, C569.1, Q54.3 (S), Q55.2 (D), R561.2, R569.1, R807.1, U53.4 (HS)
GDT2_OUT_P: C569.2, C570.2, J51.1 (PRIMARY +)
GDT2_R_HB: C563.1, U54.2 (HB)
GDT2_R_HG: Q56.1 (G), R564.2, R565.1
GDT2_R_HI: J2.5 (FPGA_IOB_22A), R511.1, R515.1
GDT2_R_HI_BUS: R515.2, U54.5 (HI)
GDT2_R_HO: R564.1, U54.3 (HO)
GDT2_R_LG: Q57.1 (G), R566.2, R567.1
GDT2_R_LO: J2.6 (FPGA_IOB_13B), R512.1, R516.1
GDT2_R_LO_BUS: R516.2, U54.6 (LI)
GDT2_R_LO_DRV: R566.1, U54.8 (LO)
GDT2_R_SW: C563.2, J51.2 (PRIMARY -), Q56.3 (S), Q57.2 (D), R565.2, R808.1, U54.4 (HS)
GDT2_SNUB: C570.1, R569.2
GND: C1.2, C2.2, C3.2, C4.2, C5.2, C6.2, C7.2, C8.2, C9.2, C10.2, C11.2, C12.2, C13.2, C14.2, C15.2, C16.2, C17.2, C18.2, C20.2, C21.2, C22.2, C300.2, C302.2, C303.2, C304.2, C305.2, C306.2, C310.2, C312.2, C313.2, C314.2, C315.2, C316.2, C335.2, C336.2, C337.2, C338.2, C339.2, C340.2, C341.2, C342.2, C400.2, C401.2, C402.2, C403.2, C404.2, C410.2, C412.2, C413.2, C421.2, C422.2, C423.2, C424.2, C427.2, C428.2, C429.2, C521.2, C522.2, C524.2, C525.2, C526.2, C531.2, C532.2, C533.2, C534.2, C535.2, C536.2, C537.2, C561.2, C562.2, C564.2, C565.2, C566.2, C571.2, C572.2, C573.2, C574.2, C575.2, C576.2, C577.2, C600.2, C601.2, C602.2, C603.2, C604.2, C610.2, C612.2, C613.2, C624.2, C627.2, C628.2, C629.2, C700.2, C701.2, C702.2, C703.2, C710.2, C711.2, C712.2, C713.2, C720.2, C721.2, C722.2, C723.2, C730.2, C731.2, C732.2, C733.2, C740.2, C741.2, D40.2, D43.1 (A1), D50.2 (A), D51.2 (A), D60.2, D63.1 (A1), D70.1 (A1), D71.1 (A1), D72.1 (A1), D73.1 (A1), D80.1 (K), D81.1 (K), D82.1 (K), D83.1 (K), D84.1 (K), D86.1 (K), D87.1 (K), D88.1 (K), D90.2 (A), D91.2 (A), D92.2 (A), D93.2 (A), J1.5 (GND), J1.6 (GND), J1.9 (GND), J1.10 (GND), J1.22 (GND), J1.30 (GND), J1.31 (GND), J2.1 (GND), J2.3 (GND), J2.8 (GND), J2.13 (GND), J2.18 (GND), J2.23 (GND), J2.28 (GND), J3.2 (GND), J5.A1 (GND), J5.A12 (GND), J5.B1 (GND), J5.B12 (GND), J5.S1 (SHIELD), J8.2 (GND), J9.2 (GND), J10.2 (GND), J30.2 (-), L40.3 (N OUT), L60.3 (N OUT), Q51.3 (S), Q53.3 (S), Q55.3 (S), Q57.3 (S), R21.1, R24.2, R25.2, R27.2, R301.2, R305.2, R311.2, R315.2, R400.2, R401.2, R415.2, R422.2, R500.2, R501.2, R502.2, R503.2, R509.2, R510.2, R511.2, R512.2, R523.2, R527.2, R563.2, R567.2, R600.2, R601.2, R615.2, R622.2, R701.2, R711.2, R721.2, R731.2, TP702.1, TP712.1, TP722.1, TP732.1, U1.2 (AGND), U1.8 (RANGE), U1.16 (UNUSED_DB), U1.17 (UNUSED_DB), U1.18 (UNUSED_DB), U1.26 (AGND), U1.30 (UNUSED_DB), U1.31 (UNUSED_DB), U1.32 (UNUSED_DB), U1.33 (UNUSED_DB), U1.35 (AGND), U1.40 (AGND), U1.41 (AGND), U1.43 (AGND), U1.46 (AGND), U1.47 (AGND), U1.50 (V1-), U1.52 (V2-), U1.54 (V3-), U1.56 (V4-), U1.58 (V5-), U1.60 (V6-), U1.62 (V7-), U1.64 (V8-), U2.2 (GND), U3.2 (GND), U30.4 (GND), U30.8 (EP), U31.4 (GND), U31.8 (EP), U40.3 (+), U41.3 (+), U42.2 (V-), U42.6 (SHDN), U44.4 (GND), U51.7 (VSS), U52.7 (VSS), U53.7 (VSS), U54.7 (VSS), U60.3 (+), U61.3 (+), U62.2 (V-), U62.6 (SHDN)
LED_80_A: D80.2 (A), R800.2
LED_81_A: D81.2 (A), R801.2
LED_82_A: D82.2 (A), R802.2
LED_83_A: D83.2 (A), R803.2
LED_84_A: D84.2 (A), D90.1 (K), R804.2
LED_86_A: D86.2 (A), D91.1 (K), R806.2
LED_87_A: D87.2 (A), D92.1 (K), R807.2
LED_88_A: D88.2 (A), D93.1 (K), R808.2
P30_FB: C301.2, R300.2, R301.1, U30.6 (FB)
P30_RON: R302.2, U30.2 (RON)
P30_SS: C300.1, U30.5 (SS)
P30_UVLO: R304.2, R305.1, U30.3 (EN)
P31_FB: C311.2, R310.2, R311.1, U31.6 (FB)
P31_RON: R312.2, U31.2 (RON)
P31_SS: C310.1, U31.5 (SS)
P31_UVLO: R314.2, R315.1, U31.3 (EN)
REGCAP_A: C6.1, U1.36 (REGCAP_A)
REGCAP_D: C7.1, U1.39 (REGCAP_D)
USB_CC1: J5.A5 (CC1), R24.1
USB_CC2: J5.B5 (CC2), R25.1
USB_D+: J1.7 (USB_D+), J5.A6 (D+), J5.B6 (D+), U3.1 (D+), U3.6 (D+)
USB_D-: J1.8 (USB_D-), J5.A7 (D-), J5.B7 (D-), U3.3 (D-), U3.4 (D-)
USB_VBUS: C22.1, J5.A4 (VBUS), J5.A9 (VBUS), J5.B4 (VBUS), J5.B9 (VBUS), R26.1, U3.5 (VBUS)
USB_VBUS_PRESENT: J1.20 (ESP_GPIO8), R26.2, R27.1
VBAT_24V: C302.1, C303.1, C312.1, C313.1, C335.1, C336.1, C337.1, C338.1, C339.1, C340.1, C341.1, C342.1, C526.1, C531.1, C532.1, C533.1, C534.1, C535.1, C536.1, C537.1, C566.1, C571.1, C572.1, C573.1, C574.1, C575.1, C576.1, C577.1, D50.1 (K), D51.1 (K), J4.1 (+), Q50.2 (D), Q52.2 (D), Q54.2 (D), Q56.2 (D), R302.1, R304.1, R312.1, R314.1, R800.1, U30.1 (VIN), U31.1 (VIN)
VIN_5V: C20.1, C311.1, C314.1, C315.1, C316.1, J1.1 (VIN_5V), J1.2 (VIN_5V), J1.3 (VIN_5V), J1.4 (VIN_5V), R20.1, R310.1, R802.1, U2.1 (VIN), U2.3 (EN), U31.7 (VOUT)

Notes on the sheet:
DAUGHTERBOARD / FPGA + ESP32
OS[2:0]=111: software mode
Configure ranges and high bandwidth before capture.
ADC / AD7606C-16
CH1-4: AUX1, AUX2, AUX3, AUX4 / 0-5 V; CH5/6 CST 1; CH7/8 CST 2
100R / 1nF: EMI filtering, not anti-alias filtering.
ANALOG INPUTS / ADC RC FILTERS
AVCC / one local capacitor at each supply pin
VDRIVE
REGCAP_A and REGCAP_D are internal-regulator outputs: bypass only.
REFCAP pins 44/45 share C9; REF pin 42 uses C8.
ADC / LOCAL BYPASS + REFERENCE
ANALOG + LOGIC SUPPLIES
PROGRAMMING ONLY - power the controller from its normal supply.
USB VBUS is isolated from VIN_5V. No USB-PD or USB-UART bridge.
VBUS presence: J1.20 / ESP GPIO8; firmware must monitor this input.
A6/B6 = D+; A7/B7 = D-. Each CC pin has its own 5.1k pulldown.
USB-C / PROGRAMMING ONLY
Input wiring: see BATTERY INPUTS / SERIES LINK + RESERVOIR.
Values and power-stage thermal performance require validation.
DESIGN NOTES
LMZ14202H: shielded inductor inside the module.
UVLO: approx. 21.0 V on / 19.4 V off; soft start 0.47 ms.
Output bank: verify DC-biased capacitance before release.
2 A device rating; thermal / load qualification pending.
24 V TO 12 V / DRIVER BIAS
24 V TO 5 V / LOGIC
8 x 22uF / 50V / 2220 reservoir
Series: J4 upper battery, J30 lower battery; pin 1 +, pin 2 -.
Single 24 V PSU: + to J4.1, - to J30.2; leave J4.2 / J30.1 unused.
BAT_MID_12V joins J4.2 to J30.1 only; it is not board ground.
BATTERY INPUTS / SERIES LINK + RESERVOIR
10R burden: 2 x 20R / nominal +/-2 V. Choose CT ratio N = 5 x primary peak amperes.
Vhalf = -max(Vct,0); U41 sums -(Vct + 2 Vhalf) = |Vct|. 1k/10nF: 10 us smoothing, not peak hold.
Keep a secondary clamp at the CT itself if the cable can unplug. Overcurrent decisions are made by the FPGA from ADC samples.
CST 1 / INPUT + PRECISION RECTIFIER
Vphase = 1.65 V + Vct/2; compare with CT1_MID.
22pF EMI filter; 6mV internal comparator hysteresis.
Timing threshold + delay must be calibrated versus amplitude.
Phase midpoint: 1.65 V. Wait >=100 ms after rails stabilize before arming.

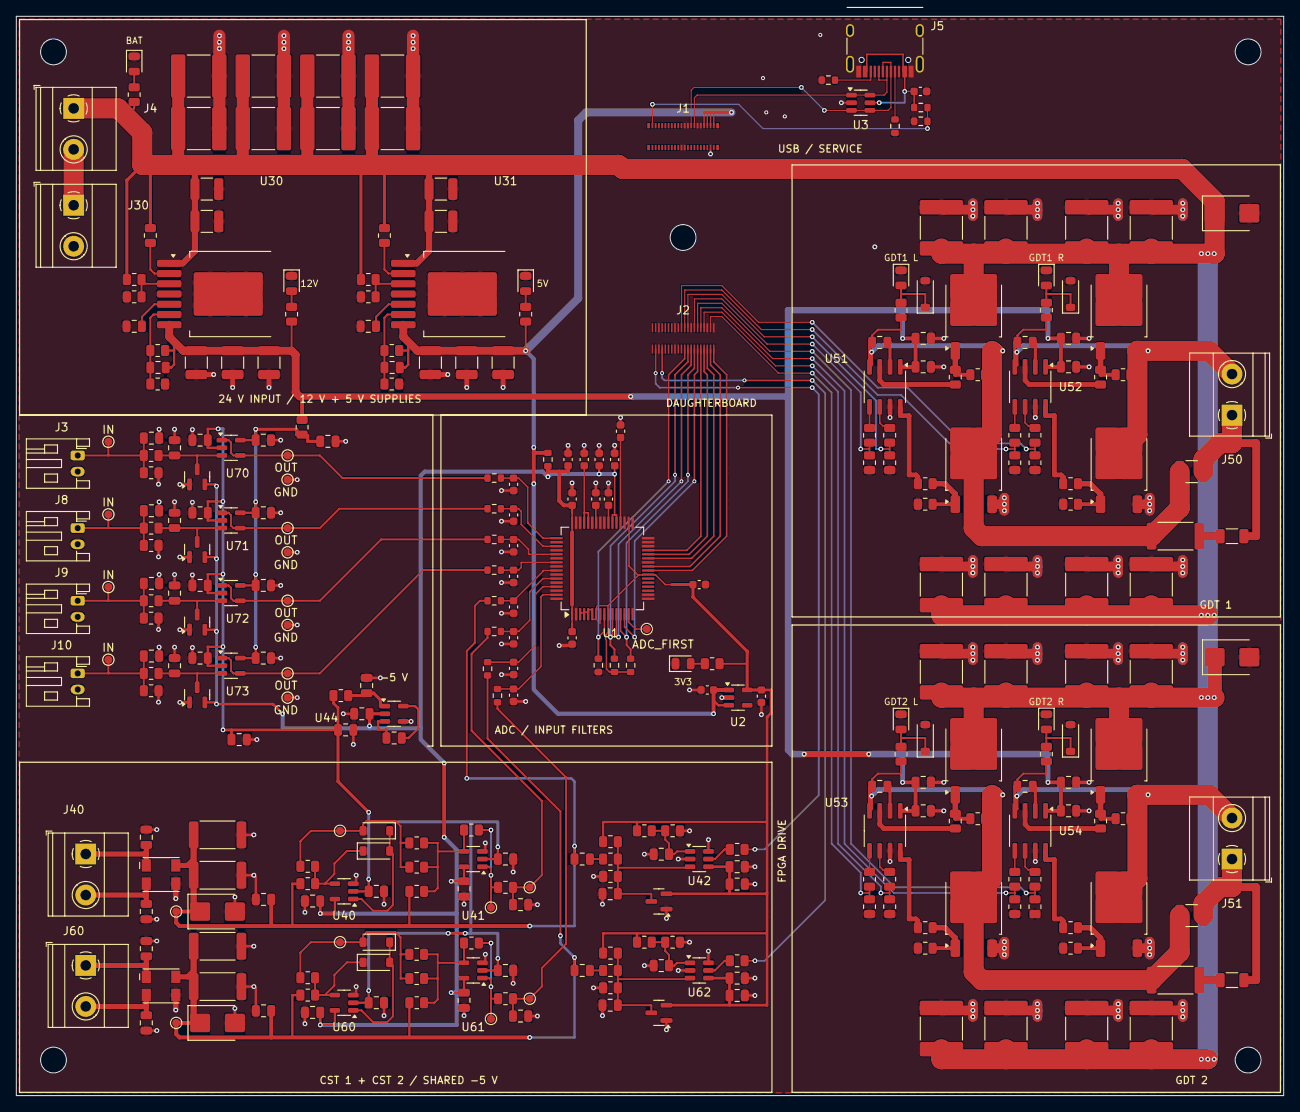
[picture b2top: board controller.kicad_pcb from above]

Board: 2 copper layers, 157.0 x 133.7 mm, 326 parts (0 on the bottom side), 141 nets.
